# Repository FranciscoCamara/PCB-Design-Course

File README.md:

# PCB Design Course

A repository containing course material, projects, and examples for learning printed circuit board (PCB) design using KiCad.

## About

This repository hosts all the materials for the **PCB Design Course** taught by Profesor Cândido Duarte. It is intended for students who want to learn the fundamentals of PCB design, from schematic capture to board layout, fabrication files, and assembly.

## Course Structure

The course is organized into projects. Each project builds on the previous one.

```text
PCB-Design-Course/
├── Projeto1/          ← First project (simple design, single layer, etc.)
├── Projeto2/          ← More advanced design (multi-layer, components, etc.)
└── README.md
```

## Projects

### Projeto1

* Description: introductory project

* What you will learn: basic schematic design, layout, design rules, generating Gerbers

* Included files: schematic (.sch), board (.brd), Gerber files

### Projeto2

* Description: intermediate / advanced design

* What you will learn: multi-layer design, routing, power planes, via strategies

* Included files: improved schematic, board files, drill files, BOM, etc.

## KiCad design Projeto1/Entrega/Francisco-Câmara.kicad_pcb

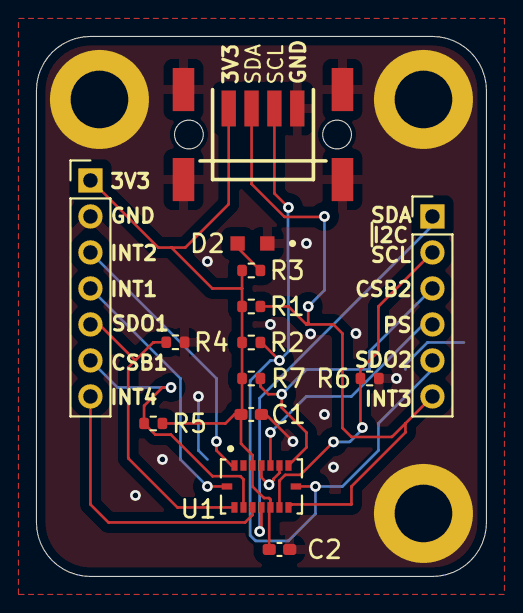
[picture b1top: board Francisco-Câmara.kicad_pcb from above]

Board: 2 copper layers, 25.0 x 30.0 mm, 14 parts (0 on the bottom side), 14 nets.

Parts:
C1, C2: 100n; C_0402_1005Metric_Pad0.74x0.62mm_HandSolder
D2: APT1608LZGCK; LED_APT1608LZGCK
J1: 284697-E; 284697E
J3: Conn_01x07_Pin; PinHeader_1x07_P2.00mm_Vertical
J4: Conn_01x06_Pin; PinHeader_1x06_P2.00mm_Vertical
R1, R2: 4k7; R_0402_1005Metric
R3: 100R; R_0402_1005Metric
R4, R5, R6, R7: 0R; R_0402_1005Metric
U1: BMI088; PQFN50P450X300X100-16N

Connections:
+3V3: C1.1, C2.1, J1.1, J3.1, R1.1, R2.1, R3.1, R5.1, R7.1, U1.3 (VDD), U1.11 (VDDIO)
CSB1: J3.6, R5.2, U1.14 (CSB1)
CSB2: J4.4, U1.5 (CSB2)
GND: C1.2, C2.2, D2.1, J1.4, J1.5 (S1), J1.6 (S2), J1.7 (S3), J1.8 (S4), J3.2, R4.2, R6.2, U1.4 (GNDA), U1.6 (GNDIO)
INT1: J3.4, U1.16 (INT1)
INT2: J3.3, U1.1 (INT2)
INT3: J4.1, U1.12 (INT3)
INT4: J3.7, U1.13 (INT4)
unnamed: D2.2, R3.2
PS: J4.3, R7.2, U1.7 (PS)
SCL: J1.3, J4.5, R2.2, U1.8 (SCL/SCK)
SDA: J1.2, J4.6, R1.2, U1.9 (SDA/SDI)
SDO1: J3.5, R4.1, U1.15 (SDO1)
SDO2: J4.2, R6.1, U1.10 (SDO2)

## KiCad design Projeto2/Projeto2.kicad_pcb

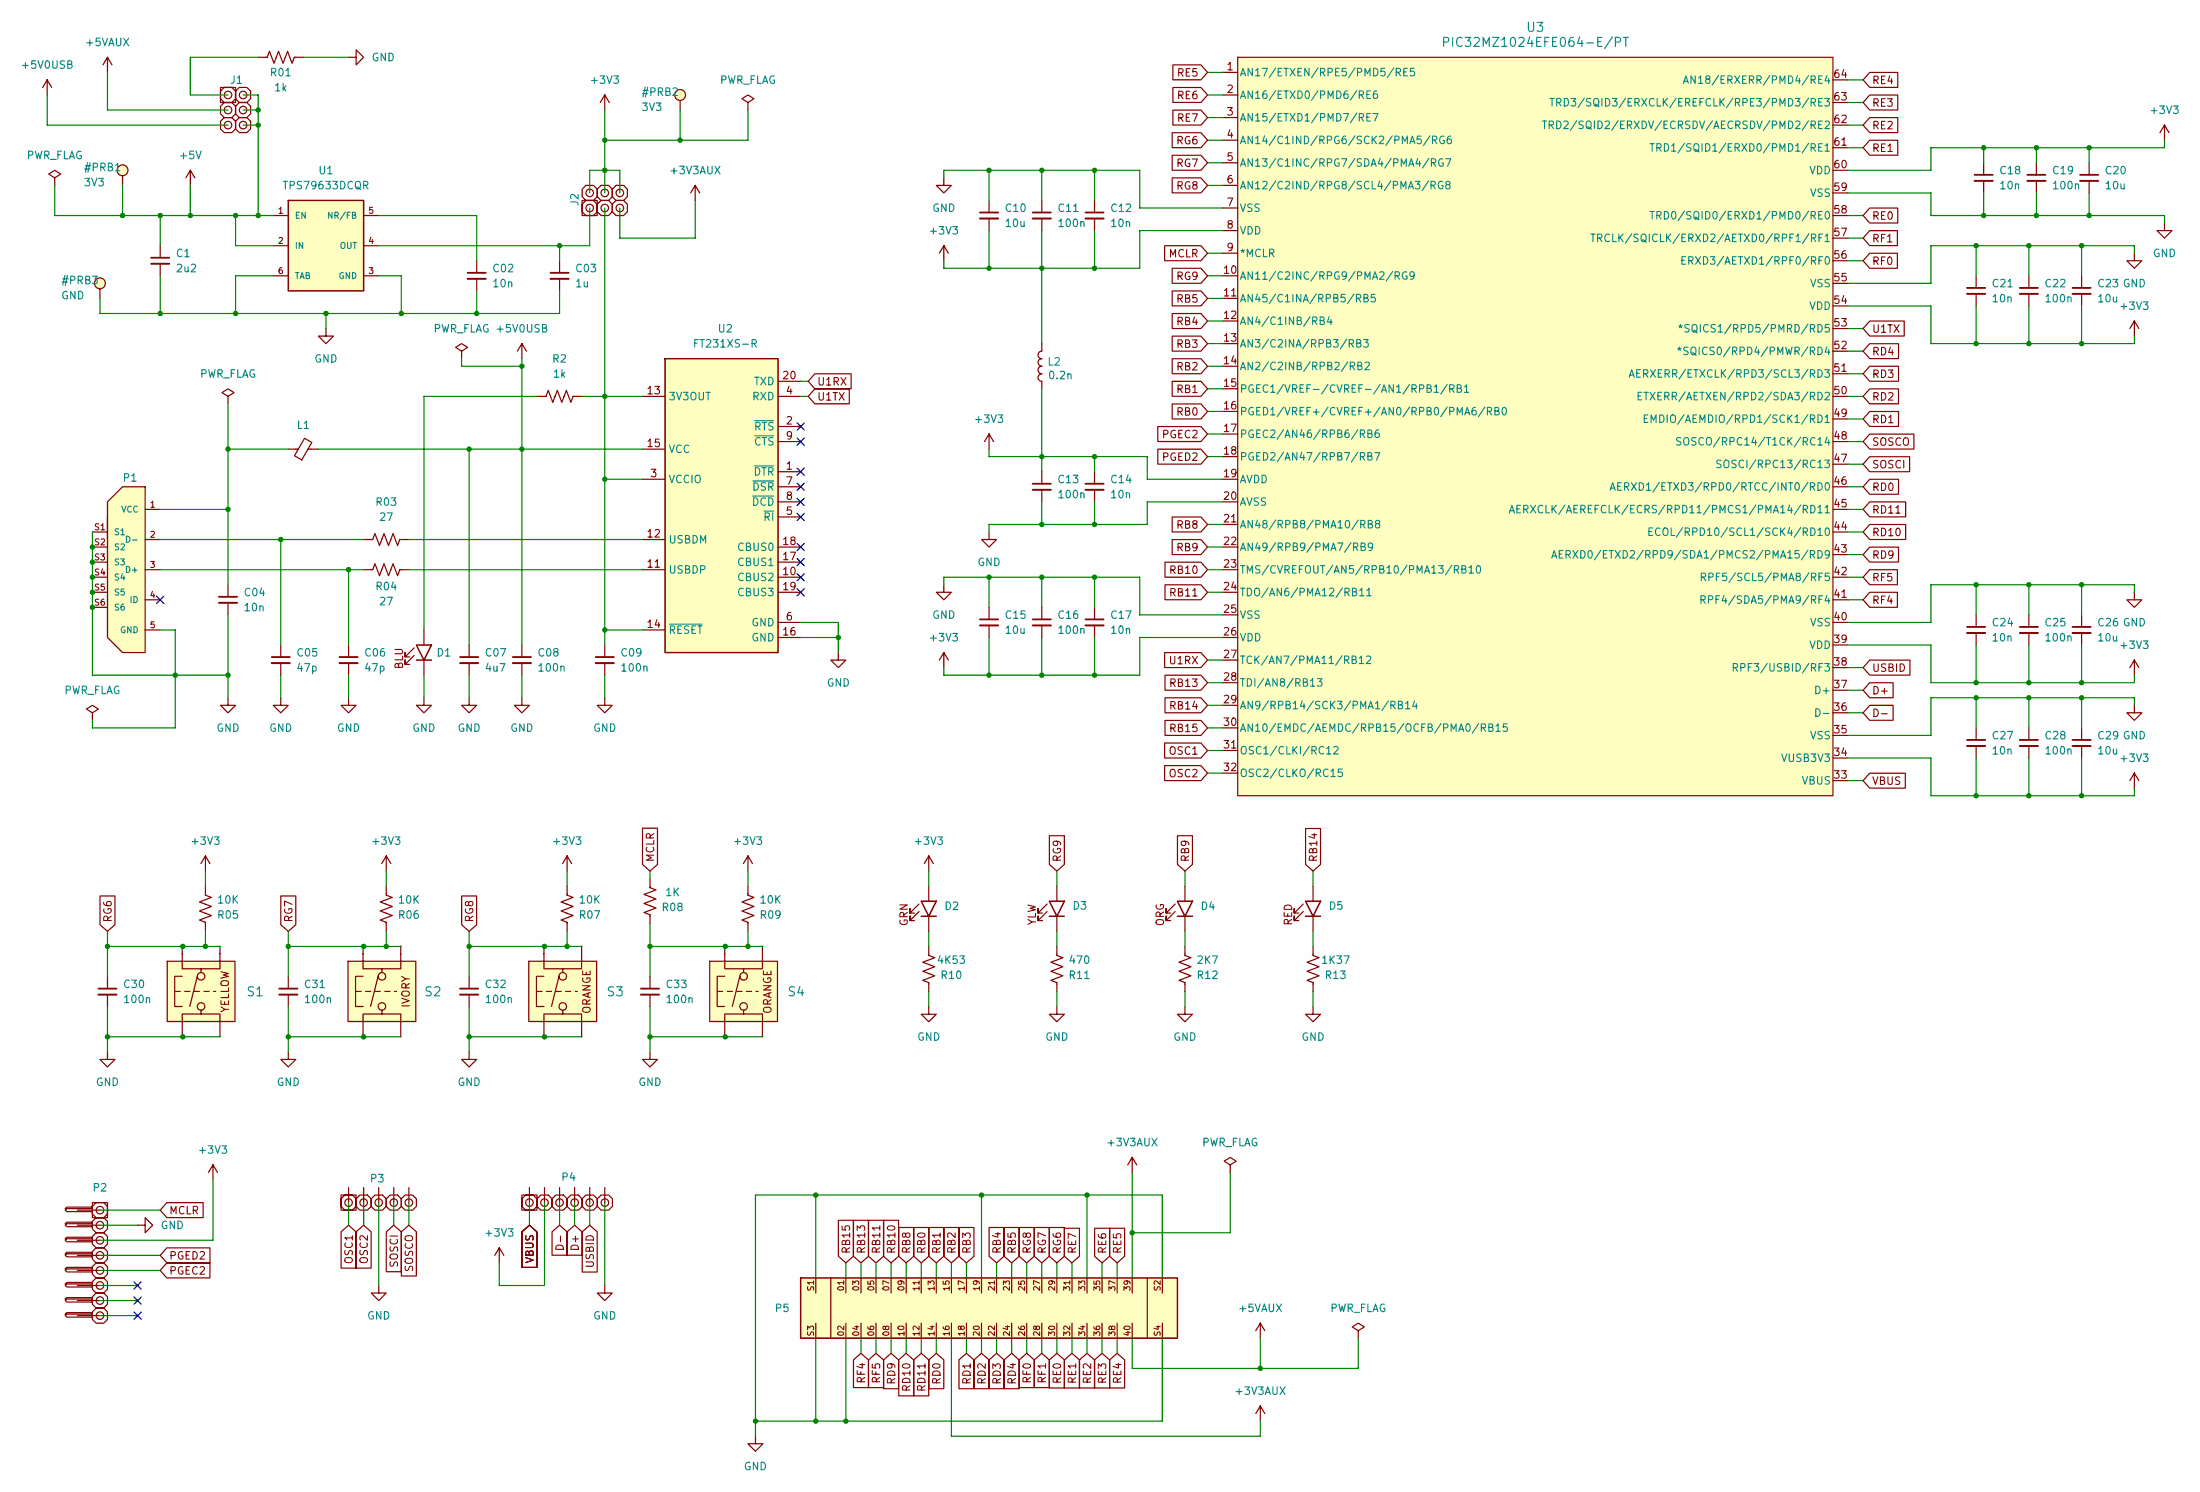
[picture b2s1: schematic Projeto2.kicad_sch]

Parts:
C1: 2u2; C_0805_2012Metric_Pad1.18x1.45mm_HandSolder
C02, C04: 10n; C_0805_2012Metric_Pad1.18x1.45mm_HandSolder
C03: 1u; C_0805_2012Metric_Pad1.18x1.45mm_HandSolder
C05, C06: 47p; C_0805_2012Metric_Pad1.18x1.45mm_HandSolder
C07: 4u7; C_0603_1608Metric_Pad1.08x0.95mm_HandSolder
C08, C09, C11, C13, C16, C19, C22, C25, C28, C30, C31, C32, C33: 100n; C_0603_1608Metric_Pad1.08x0.95mm_HandSolder
C10, C15, C20, C23, C26, C29: 10u; C_0805_2012Metric_Pad1.18x1.45mm_HandSolder
C12, C14, C17, C18, C21, C24, C27: 10n; C_0603_1608Metric_Pad1.08x0.95mm_HandSolder
D1: LED_BLUE; LED_APT1608LVBC_D
D2: LED_GREEN; LED_APT1608LVBC_D
D3: LED_YELLOW; LED_APT1608LVBC_D
D4: LED_ORANGE; LED_APT1608LVBC_D
D5: LED_RED; LED_APT1608LVBC_D
J1, J2: Conn_02x03_Odd_Even; PinHeader_2x03_P2.54mm_Vertical
L1: FerriteBead_Small; L_0603_1608Metric_Pad1.05x0.95mm_HandSolder
L2: 0.2n; L_0402_1005Metric_Pad0.77x0.64mm_HandSolder
P1: 10118194-0001LF; AMPHENOL_10118194-0001LF; PARTREV D
P2: Conn_01x08_Pin; PinHeader_1x08_P2.54mm_Horizontal
P3: Conn_01x05_Pin; PinHeader_1x05_P2.54mm_Vertical
P4: Conn_01x06_Pin; PinHeader_1x06_P2.54mm_Vertical
P5: HSEC8-120-01-S-D-EM2; SAMTEC_HSEC8-120-01-S-D-EM2
R01, R2: 1k; R_0603_1608Metric_Pad0.98x0.95mm_HandSolder
R03, R04: 27; R_0603_1608Metric_Pad0.98x0.95mm_HandSolder
R05, R06, R07, R09: 10K; R_0603_1608Metric_Pad0.98x0.95mm_HandSolder
R08: 1K; R_0603_1608Metric_Pad0.98x0.95mm_HandSolder
R10: 4K53; R_0603_1608Metric_Pad0.98x0.95mm_HandSolder
R11: 470; R_0603_1608Metric_Pad0.98x0.95mm_HandSolder
R12: 2K7; R_0603_1608Metric_Pad0.98x0.95mm_HandSolder
R13: 1K37; R_0603_1608Metric_Pad0.98x0.95mm_HandSolder
S1: B3F-1002; SW_B3F-1000_OMR
S2: B3F-1000; SW_B3F-1000_OMR
S3, S4: B3F-1005; SW_B3F-1000_OMR
U1: TPS79633DCQR; VREG_TPS79633DCQR; PARTREV P
U2: FT231XS-R; SSOP-20_3.9x8.7mm_P0.635mm
U3: PIC32MZ1024EFE064-E/PT; TQFP64_PT_MCH

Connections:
+3V3AUX: J2.5, P5.16, P5.39
+5V0USB: C07.1, C08.1, J1.5, L1.2, U2.15 (VCC)
+5VAUX: J1.3, P5.40
D+: P4.4, U3.37 (D+)
D-: P4.3, U3.36 (D-)
GND: C1.2, C02.2, C03.2, C04.2, C05.2, C06.2, C07.2, C08.2, C09.2, C10.1, C11.1, C12.1, C13.2, C14.2, C15.1, C16.1, C17.1, C18.2, C19.2, C20.2, C21.1, C22.1, C23.1, C24.1, C25.1, C26.1, C27.1, C28.1, C29.1, C30.2, C31.2, C32.2, C33.2, D1.1 (K), P1.5 (GND), P1.S1, P1.S2, P1.S3, P1.S4, P1.S5, P1.S6, P1.SH1, P1.SH2, P1.SH3, P1.SH4, P1.SH5, P1.SH6, P2.2, P3.3, P4.6, P5.02, P5.19, P5.33, P5.S1, P5.S2, P5.S3, P5.S4, R01.2, R10.1, R11.1, R12.1, R13.1, S1.2, S1.4, S2.2, S2.4, S3.2, S3.4, S4.2, S4.4, U1.3 (GND), U1.6 (TAB), U1.7, U1.8, U1.9, U1.10, U1.11, U1.12, U1.13, U1.14, U1.15, U1.16, U2.6 (GND), U2.16 (GND), U3.7 (VSS), U3.20 (AVSS), U3.25 (VSS), U3.35 (VSS), U3.40 (VSS), U3.55 (VSS), U3.59 (VSS); also elsewhere on the board
MCLR: P2.1, R08.2, U3.9 (*MCLR)
unnamed: C33.1, R08.1, R09.1, S4.1, S4.3
unnamed: D1.2 (A), R2.1
unnamed: D2.1 (K), R10.2
unnamed: D3.1 (K), R11.2
unnamed: D4.1 (K), R12.2
unnamed: D5.1 (K), R13.2
unnamed: J1.1, R01.1
unnamed: C03.1, J2.1, U1.4 (OUT)
unnamed: C09.1, J2.3, R2.2, U2.3 (VCCIO), U2.13 (3V3OUT), U2.14 (~RESET)
unnamed: C06.1, P1.3 (D+), R04.1
unnamed: C05.1, P1.2 (D-), R03.1
unnamed: C04.1, L1.1, P1.1 (VCC)
unnamed: C02.1, U1.5 (NR/FB)
unnamed: R03.2, U2.12 (USBDM)
unnamed: R04.2, U2.11 (USBDP)
OSC1: P3.1, U3.31 (OSC1/CLKI/RC12)
OSC2: P3.2, U3.32 (OSC2/CLKO/RC15)
PGEC2: P2.5, U3.17 (PGEC2/AN46/RPB6/RB6)
PGED2: P2.4, U3.18 (PGED2/AN47/RPB7/RB7)
RB0: P5.11, U3.16 (PGED1/VREF+/CVREF+/AN0/RPB0/PMA6/RB0)
RB1: P5.13, U3.15 (PGEC1/VREF-/CVREF-/AN1/RPB1/RB1)
RB2: P5.15, U3.14 (AN2/C2INB/RPB2/RB2)
RB3: P5.17, U3.13 (AN3/C2INA/RPB3/RB3)
RB4: P5.21, U3.12 (AN4/C1INB/RB4)
RB5: P5.23, U3.11 (AN45/C1INA/RPB5/RB5)
RB8: P5.09, U3.21 (AN48/RPB8/PMA10/RB8)
RB9: D4.2 (A), U3.22 (AN49/RPB9/PMA7/RB9)
RB10: P5.07, U3.23 (TMS/CVREFOUT/AN5/RPB10/PMA13/RB10)
RB11: P5.05, U3.24 (TDO/AN6/PMA12/RB11)
RB13: P5.03, U3.28 (TDI/AN8/RB13)
RB14: D5.2 (A), U3.29 (AN9/RPB14/SCK3/PMA1/RB14)
RB15: P5.01, U3.30 (AN10/EMDC/AEMDC/RPB15/OCFB/PMA0/RB15)
RD0: P5.14, U3.46 (AERXD1/ETXD3/RPD0/RTCC/INT0/RD0)
RD1: P5.18, U3.49 (EMDIO/AEMDIO/RPD1/SCK1/RD1)
RD2: P5.20, U3.50 (ETXERR/AETXEN/RPD2/SDA3/RD2)
RD3: P5.22, U3.51 (AERXERR/ETXCLK/RPD3/SCL3/RD3)
RD4: P5.24, U3.52 (*SQICS0/RPD4/PMWR/RD4)
RD9: P5.08, U3.43 (AERXD0/ETXD2/RPD9/SDA1/PMCS2/PMA15/RD9)
RD10: P5.10, U3.44 (ECOL/RPD10/SCL1/SCK4/RD10)
RD11: P5.12, U3.45 (AERXCLK/AEREFCLK/ECRS/RPD11/PMCS1/PMA14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)
RE0: P5.30, U3.58 (TRD0/SQID0/ERXD1/PMD0/RE0)
RE1: P5.32, U3.61 (TRD1/SQID1/ERXD0/PMD1/RE1)
RE2: P5.34, U3.62 (TRD2/SQID2/ERXDV/ECRSDV/AECRSDV/PMD2/RE2)
RE3: P5.36, U3.63 (TRD3/SQID3/ERXCLK/EREFCLK/RPE3/PMD3/RE3)
RE4: P5.38, U3.64 (AN18/ERXERR/PMD4/RE4)
RE5: P5.37, U3.1 (AN17/ETXEN/RPE5/PMD5/RE5)
RE6: P5.35, U3.2 (AN16/ETXD0/PMD6/RE6)
RE7: P5.31, U3.3 (AN15/ETXD1/PMD7/RE7)
RF0: P5.26, U3.56 (ERXD3/AETXD1/RPF0/RF0)
RF1: P5.28, U3.57 (TRCLK/SQICLK/ERXD2/AETXD0/RPF1/RF1)
RF4: P5.04, U3.41 (RPF4/SDA5/PMA9/RF4)
RF5: P5.06, U3.42 (RPF5/SCL5/PMA8/RF5)
RG6: C30.1, P5.29, R05.1, S1.1, S1.3, U3.4 (AN14/C1IND/RPG6/SCK2/PMA5/RG6)
RG7: C31.1, P5.27, R06.1, S2.1, S2.3, U3.5 (AN13/C1INC/RPG7/SDA4/PMA4/RG7)
RG8: C32.1, P5.25, R07.1, S3.1, S3.3, U3.6 (AN12/C2IND/RPG8/SCL4/PMA3/RG8)
RG9: D3.2 (A), U3.10 (AN11/C2INC/RPG9/PMA2/RG9)
SOSCI: P3.4, U3.47 (SOSCI/RPC13/RC13)
SOSCO: P3.5, U3.48 (SOSCO/RPC14/T1CK/RC14)
U1RX: U2.20 (TXD), U3.27 (TCK/AN7/PMA11/RB12)
U1TX: U2.4 (RXD), U3.53 (*SQICS1/RPD5/PMRD/RD5)
USBID: P4.5, U3.38 (RPF3/USBID/RF3)
VBUS: P4.1, U3.33 (VBUS)

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
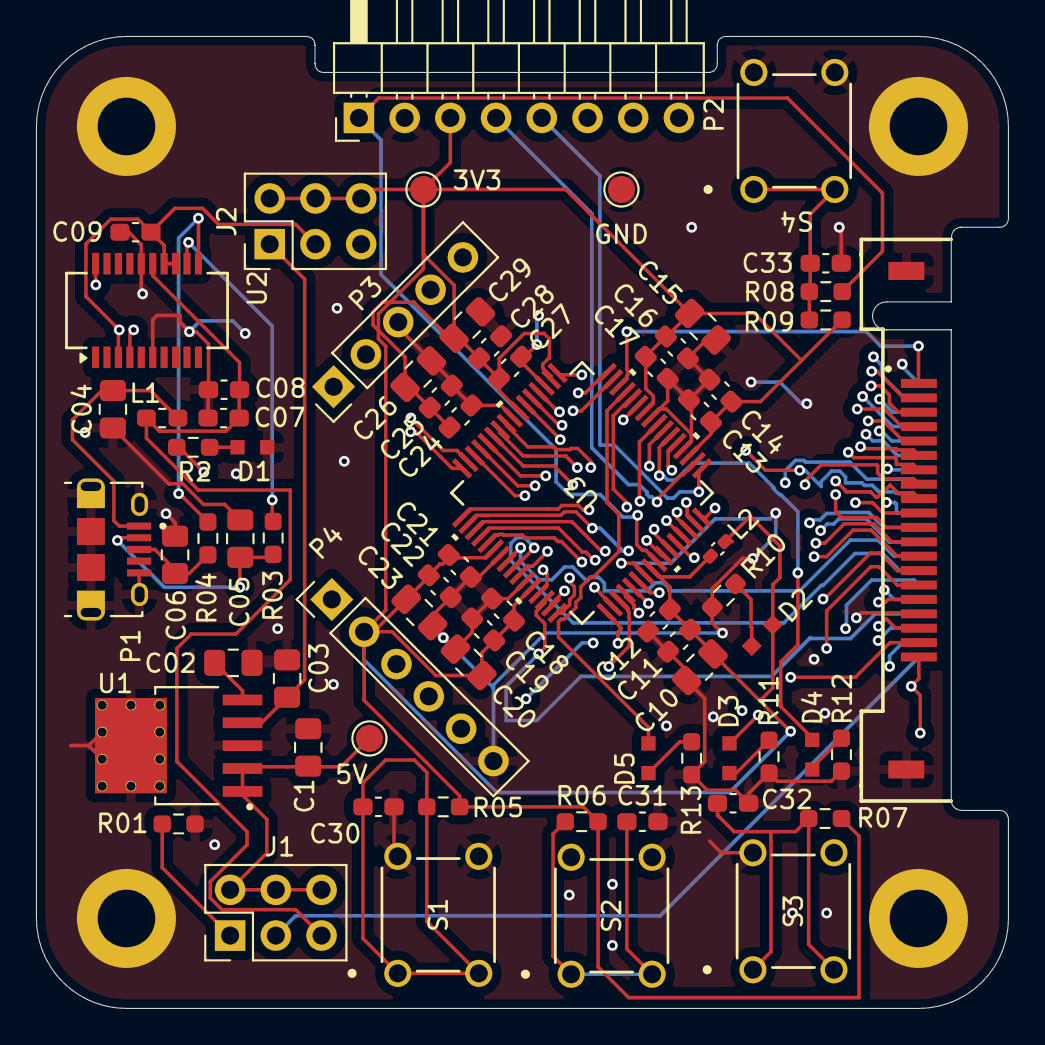
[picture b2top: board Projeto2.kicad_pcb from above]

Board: 4 copper layers, 54.0 x 54.0 mm, 70 parts (0 on the bottom side), 71 nets.

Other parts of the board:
3V3, 5V: TestPoint_Pad_D1.5mm
GND: TestPoint_Pad_D1.5mm

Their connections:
GND: GND.1; also elsewhere on the board

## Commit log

2025-06-07 Projeto2 adicionado
2025-06-07 Files added
2025-06-09 step by step
2025-06-10 more
2025-06-17 added files from project 1
2025-06-22 ahhhhhhhhhhhhhhh
2025-06-22 Projeto1 Acabado
2025-06-24 another one
2025-06-26 project 2 done
2025-09-28 Coiso?
